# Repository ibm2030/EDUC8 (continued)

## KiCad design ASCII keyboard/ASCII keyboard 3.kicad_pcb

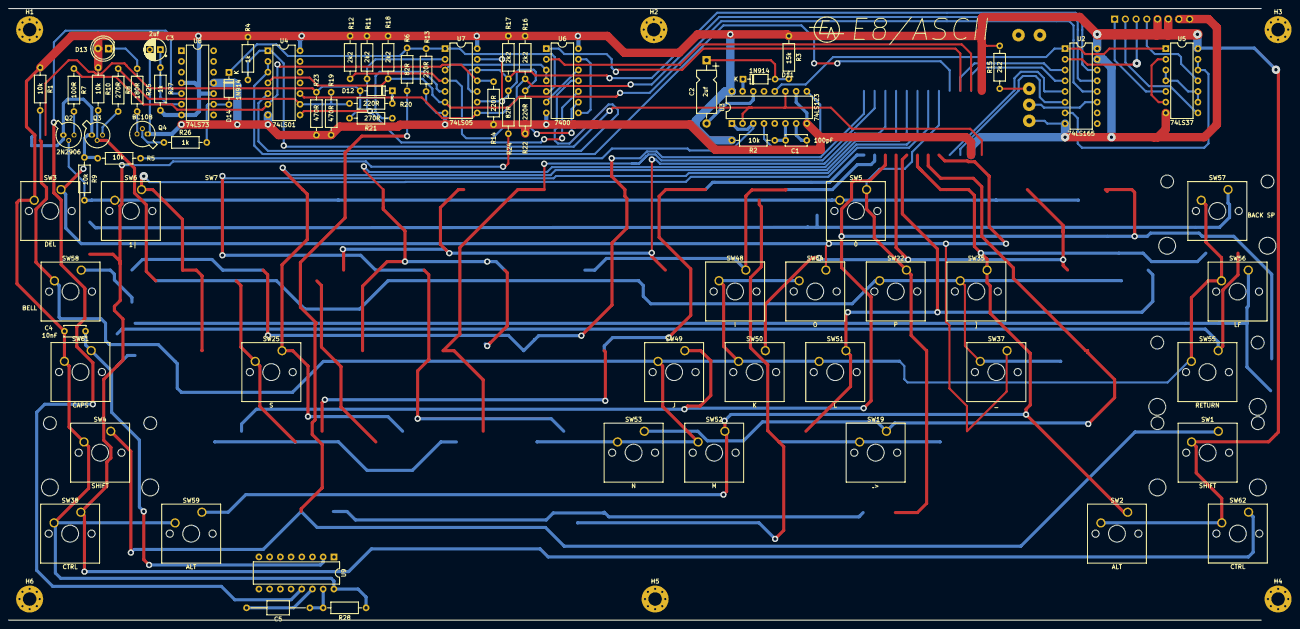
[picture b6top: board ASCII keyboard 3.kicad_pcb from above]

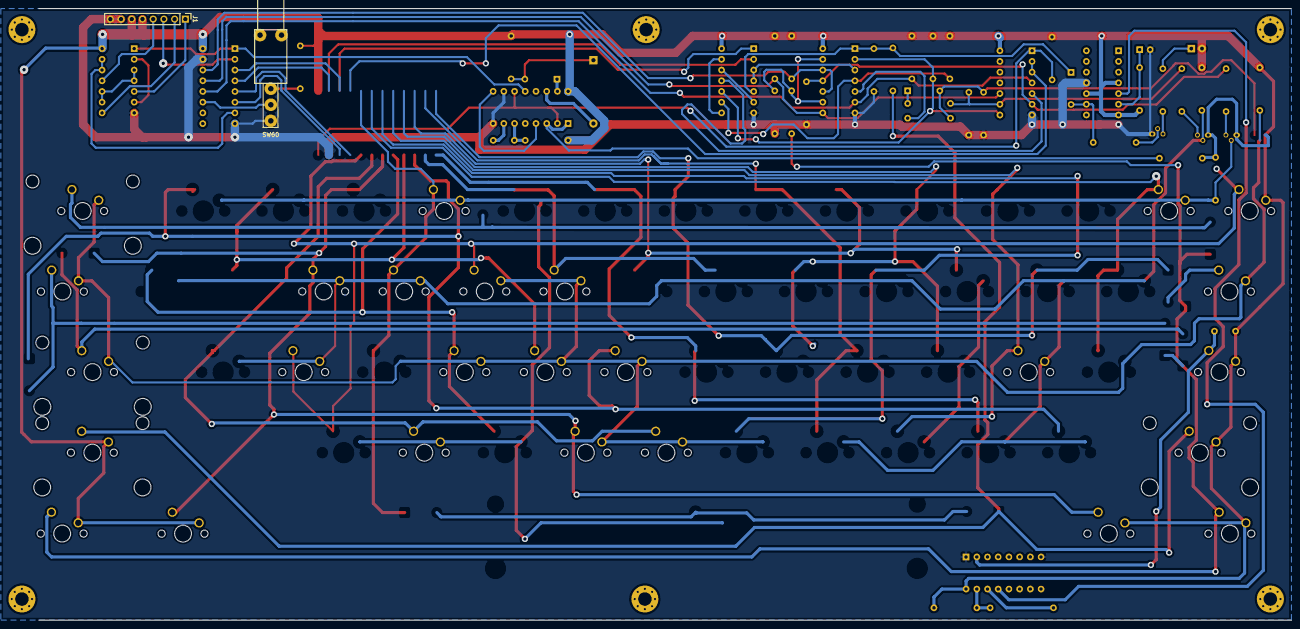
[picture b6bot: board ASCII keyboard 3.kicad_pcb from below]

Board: 2 copper layers, 297.0 x 145.0 mm, 83 parts (2 on the bottom side), 60 nets.

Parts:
C1: 100pF; C_Disc_D5.0mm_W2.5mm_P5.00mm
C2: 2uf; CP_Axial_L10.0mm_D4.5mm_P15.00mm_Horizontal
C3: 2uf; CP_Radial_D5.0mm_P2.50mm
C4: 10nF; C_Disc_D5.0mm_W2.5mm_P5.00mm
C5: 2uf; C_Axial_L5.1mm_D3.1mm_P15.00mm_Horizontal
D11, D12, D14: 1N914; D_DO-35_SOD27_P7.62mm_Horizontal
D13: LED; LED_D5.0mm
H1, H2, H3, H4, H5, H6: MountingHole_Pad; MountingHole_3.2mm_M3_Pad_Via
J1: Conn_01x08_Male; PinHeader_1x08_P2.54mm_Vertical
Q2, Q3: 2N2906; TO-18-3
Q4: BC108; TO-18-3
R1, R2, R5, R9, R10: 10k; R_Axial_DIN0207_L6.3mm_D2.5mm_P10.16mm_Horizontal
R3: 15k; R_Axial_DIN0207_L6.3mm_D2.5mm_P10.16mm_Horizontal
R4, R26, R27: 1k; R_Axial_DIN0207_L6.3mm_D2.5mm_P10.16mm_Horizontal
R6, R24: 82R; R_Axial_DIN0207_L6.3mm_D2.5mm_P10.16mm_Horizontal
R7: 100R; R_Axial_DIN0207_L6.3mm_D2.5mm_P10.16mm_Horizontal
R8, R21: 270R; R_Axial_DIN0207_L6.3mm_D2.5mm_P10.16mm_Horizontal
R11, R12, R15, R16, R17, R18: 2k2; R_Axial_DIN0207_L6.3mm_D2.5mm_P10.16mm_Horizontal
R13, R14, R20, R22, R28: 220R; R_Axial_DIN0207_L6.3mm_D2.5mm_P10.16mm_Horizontal
R19, R23: 470R; R_Axial_DIN0207_L6.3mm_D2.5mm_P10.16mm_Horizontal
R25: 180R; R_Axial_DIN0207_L6.3mm_D2.5mm_P10.16mm_Horizontal
SW1, SW4: SHIFT; SW_Cherry_MX_2.25u_PCB
SW2, SW59: ALT; SW_Cherry_MX_1.50u_PCB
SW3: DEL; SW_Cherry_MX_1.00u_PCB
SW5: 0; SW_Cherry_MX_1.00u_PCB
SW6: 1|; SW_Cherry_MX_1.00u_PCB
SW7: 2; SW_Cherry_MX_1.00u_PCB
SW19: .>; SW_Cherry_MX_1.00u_PCB
SW22: P; SW_Cherry_MX_1.00u_PCB
SW25: S; SW_Cherry_MX_1.00u_PCB
SW35: ]; SW_Cherry_MX_1.00u_PCB
SW37: _; SW_Cherry_MX_1.00u_PCB
SW38, SW62: CTRL; SW_Cherry_MX_1.50u_PCB
SW48: I; SW_Cherry_MX_1.00u_PCB
SW49: J; SW_Cherry_MX_1.00u_PCB
SW50: K; SW_Cherry_MX_1.00u_PCB
SW51: L; SW_Cherry_MX_1.00u_PCB
SW52: M; SW_Cherry_MX_1.00u_PCB
SW53: N; SW_Cherry_MX_1.00u_PCB
SW54: O; SW_Cherry_MX_1.00u_PCB
SW55: RETURN; SW_Cherry_MX_2.25u_PCB
SW56: LF; SW_Cherry_MX_1.50u_PCB
SW57: BACK SP; SW_Cherry_MX_2.00u_PCB
SW58: BELL; SW_Cherry_MX_1.50u_PCB
SW60: SW_SPDT; S1320_SPDP_Toggle_switch_PCB_right_angle
SW61: CAPS; SW_Cherry_MX_1.75u_PCB
U2: 74LS165; DIP-16_W7.62mm
U3, U9: 74LS123; DIP-16_W7.62mm
U4: 74LS01; DIP-14_W7.62mm
U5: 74LS37; DIP-14_W7.62mm
U6: 7400; DIP-14_W7.62mm
U7: 74LS05; DIP-14_W7.62mm
U8: 74LS73; DIP-14_W7.62mm

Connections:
+5V: C4.1, D13.2, J1.5, J1.6, Q2.1, Q3.1, R1.1, R2.2, R3.1, R4.1, R5.2, R9.1, R10.1, R11.1, R12.1, R15.2, R16.1, R17.1, R18.1, R27.1, R28.1, SW1.2, SW2.2, SW3.2, SW4.2, SW38.2, SW59.2, SW61.2, SW62.2, U2.16, U3.16, U4.14, U5.14, U6.14, U7.14, U8.4, U8.7, U8.10, U9.16
/A: SW5.1, SW22.1
/N: SW2.1, SW35.1, SW52.1, SW59.1
/P: SW19.1, SW53.1
/Q: SW3.1, SW37.1, SW54.1
/ROW_A: Q2.2, R9.2, SW5.2, SW6.2, SW19.2
/ROW_B: Q3.2, R10.2, SW22.2, SW25.2, SW35.2, SW37.2
/ROW_C: R1.2, SW48.2, SW49.2, SW50.2, SW51.2, SW52.2, SW53.2, SW54.2, SW55.2, SW56.2, SW57.2, SW58.2
CAPS_LOCK: C4.2, SW61.1, U9.2
CAPS_LOCK_PULSE: U8.5, U9.13
GND: C3.2, J1.7, J1.8, Q4.1, R13.2, R14.2, R19.2, R22.2, R23.2, SW60.1, U2.8, U2.15, U3.8, U3.10, U4.7, U5.7, U6.7, U7.7, U8.11, U9.1, U9.8
unnamed: C1.1, R2.1, U3.6
unnamed: C1.2, U3.7
unnamed: C2.1, D11.2, R3.2
unnamed: C2.2, U3.14
unnamed: C3.1, R27.2, U8.6
unnamed: C5.1, R28.2, U9.15
unnamed: C5.2, U9.14
unnamed: R6.2, SW1.1, SW4.1
unnamed: R24.2, SW38.1, SW62.1
unnamed: D11.1, U3.15
unnamed: D12.1, R20.2
unnamed: D12.2, R21.2, R23.1
unnamed: D13.1, R25.1
unnamed: D14.1, R6.1, R13.1, U6.5, U7.1
unnamed: D14.2, R26.2, U8.9
unnamed: H1.1, H2.1, H3.1, H4.1, H5.1, H6.1
unnamed: Q2.3, R7.2
unnamed: Q3.3, R8.2
unnamed: Q4.2, R26.1
unnamed: Q4.3, R25.2
unnamed: R4.2, U3.2, U3.11, U4.1
unnamed: R5.1, U3.1, U3.3
unnamed: R11.2, U4.8, U6.10, U7.2
unnamed: R12.2, U6.9, U7.4
unnamed: R7.1, R14.1, U4.6, U7.11
unnamed: R15.1, SW60.3
unnamed: R8.1, R19.1, R20.1, U4.9
unnamed: R21.1, U7.5
unnamed: R22.1, R24.1, U7.9, U7.13
unnamed: U2.4, U6.2
unnamed: U2.3, U6.1
unnamed: U4.2, U4.3
unnamed: U2.7, U5.12, U5.13
unnamed: U3.4, U3.9
unnamed: U4.5, U6.11
unnamed: U5.2, U5.6
unnamed: U5.3, U5.4, U5.9, U5.10
unnamed: U6.3, U6.4, U7.3
unnamed: U6.6, U6.12
unnamed: U6.8, U6.13
PA: SW60.2, U2.11
PB: R18.2, U2.12, U4.4, U7.6
PC: R16.2, U2.13, U4.10, U7.8
PD: R17.2, U2.14, U7.10, U7.12
SI: U2.1, U3.12, U5.1
~CLOCK: J1.3, U2.2
~DATA: J1.4, U5.11
~FLAG: J1.2, U5.8
~FLAG_RESET: J1.1, U5.5
